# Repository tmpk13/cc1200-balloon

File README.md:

# cc1200-balloon

High altitude balloon payload: a CC1200 434 MHz telemetry downlink, an
AT6558R GNSS receiver and an air quality sensor stack, hosted by a Seeed
Wio-E5 module on a four-layer 50 x 30 mm KiCad board. The board is routed
but not cleared for fabrication: read the verdict table in `BOARD_REVIEW.md`
before ordering. The hand-edited `.kicad_sch` files are the source of truth;
`build.sh` and `sheets/*.json` still describe the 2026-09-06 design, so do
not run `build.sh`: it would overwrite all four sheets with it.

- `mise run erc`: full-hierarchy ERC into `build/erc.rpt`
- `mise run drc`: DRC with zones refilled in memory and schematic parity, into `build/drc.rpt`
- `mise run fields-check`: report the part fields `mise run fields` would change
- `mise run fields`: write `Datasheet`, `MPN` and `Manufacturer` from `tools/parts.json` into the sheets and the board
- `mise run bom`: regenerate `digikey_bom.csv`, `BOM.md` and `bom.json` from the schematic
- `mise run power`: battery budget for the as-built, LDO and switched-domain power options
- `mise run test`: tests for the power budget and the label localizer

`mise tasks` lists the rest. Components: ARCHITECTURE.md. Open items: TODO.md.

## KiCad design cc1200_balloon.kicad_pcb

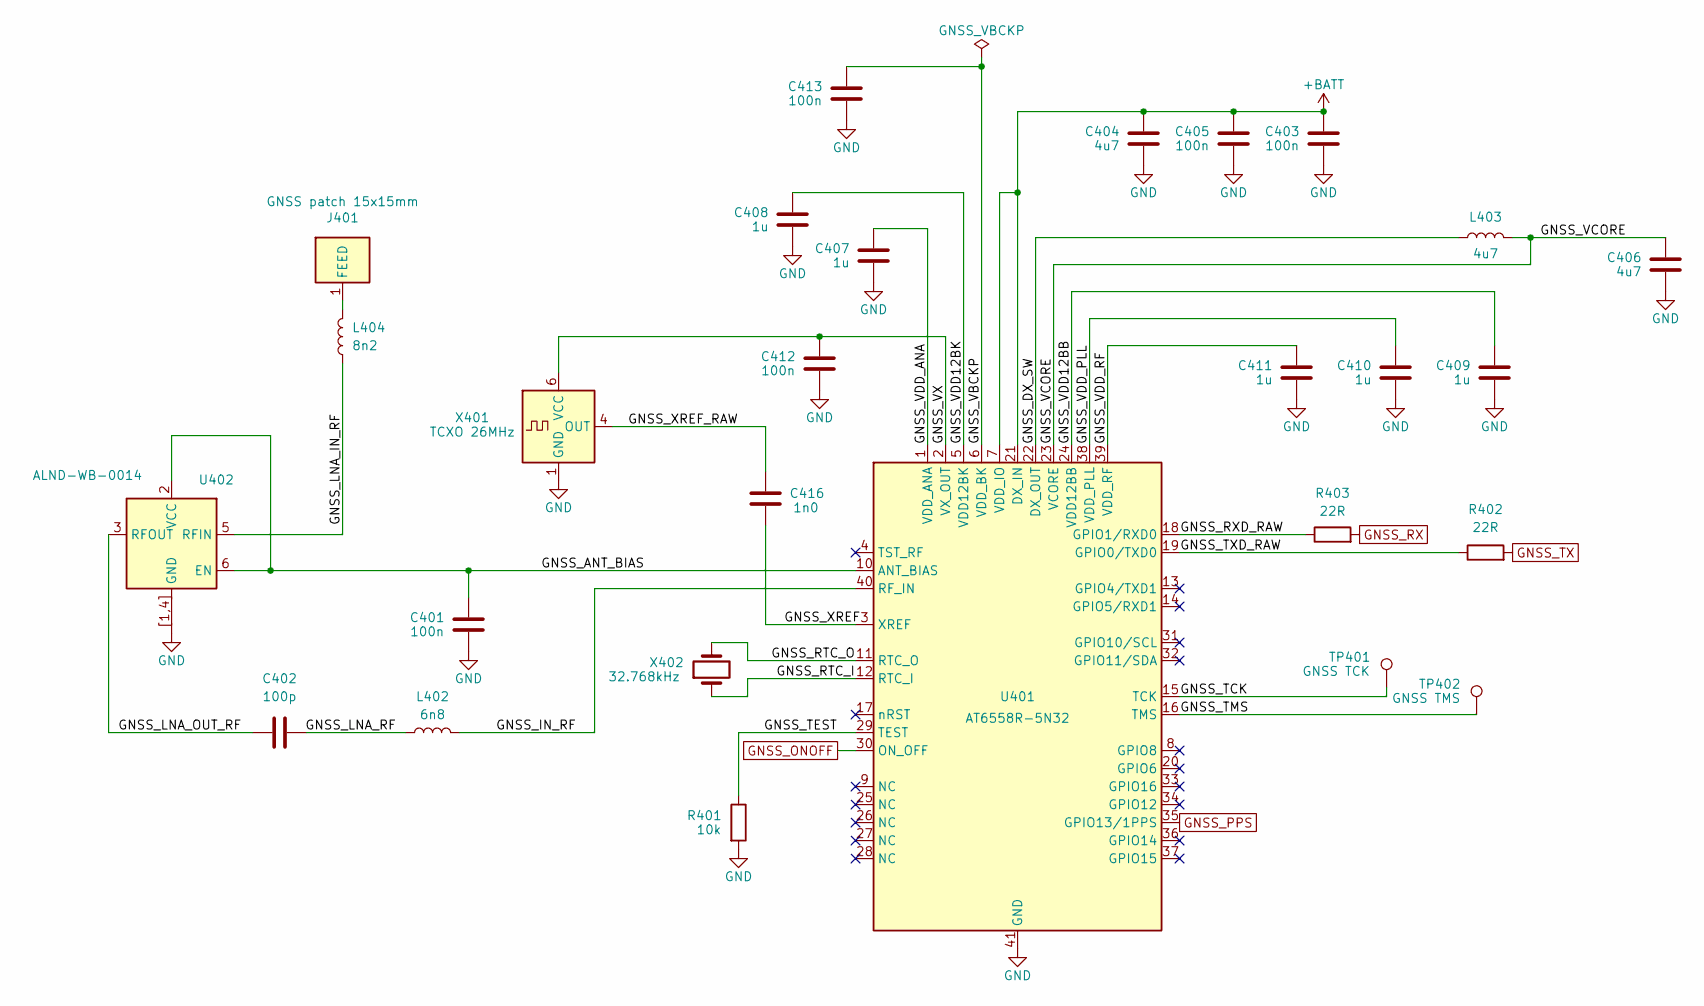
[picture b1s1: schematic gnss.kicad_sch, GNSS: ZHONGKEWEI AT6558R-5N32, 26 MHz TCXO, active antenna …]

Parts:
C401, C403, C405, C412, C413: 100n; C_0402_1005Metric; MPN CL05B104KO5NNNC
C402: 100p; C_0402_1005Metric; MPN GRM1555C1H101JA01D
C404, C406: 4u7; C_0603_1608Metric; MPN LMK107BJ475KAHT
C407, C408, C409, C410, C411: 1u; C_0402_1005Metric; MPN LMK105BJ105KVHF
C416: 1n0; C_0402_1005Metric; MPN CL05C102JB5NNNC
J401: GNSS patch 15x15mm; Patch_AC33154-1T_15x15mm; MPN AC33154-1T
L402: 6n8; L_0402_1005Metric; MPN LQW15AN6N8H00D
L403: 4u7; L_0603_1608Metric; MPN LQM18PN4R7MFRL
L404: 8n2; L_0402_1005Metric; MPN LQW15AN8N2H00D
R401: 10k; R_0402_1005Metric; MPN RC0402FR-0710KL
R402, R403: 22R; R_0402_1005Metric; MPN RC0402FR-0722RL
TP401: GNSS TCK; TestPoint_Pad_1.0x1.0mm
TP402: GNSS TMS; TestPoint_Pad_1.0x1.0mm
U401: AT6558R-5N32; AT6558R_QFN-40-1EP_5x5mm_P0.4mm_EP3.4x3.4mm; MPN AT6558R-5N32
U402: ALND-WB-0014; Abracon_DFN-6_1.1x0.7mm; MPN ALND-WB-0014-T
X401: TCXO 26MHz; Oscillator_SMD_Kyocera_2520-6Pin_2.5x2.0mm; MPN NSC5351B-26M
X402: 32.768kHz; Crystal_SMD_3215-2Pin_3.2x1.5mm; MPN FC3215AN 32.768K-90NN60KC5

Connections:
+BATT: C403.1, C404.1, C405.1, U401.7 (VDD_IO), U401.21 (DX_IN); also elsewhere on the board
/GNSS/GNSS_ANT_BIAS: C401.1, U401.10 (ANT_BIAS), U402.2 (VCC), U402.6 (EN)
/GNSS/GNSS_DX_SW: L403.1, U401.22 (DX_OUT)
/GNSS/GNSS_IN_RF: L402.2, U401.40 (RF_IN)
/GNSS/GNSS_LNA_IN_RF: L404.1, U402.5 (RFIN)
/GNSS/GNSS_LNA_OUT_RF: C402.1, U402.3 (RFOUT)
/GNSS/GNSS_LNA_RF: C402.2, L402.1
/GNSS/GNSS_RTC_I: U401.12 (RTC_I), X402.1
/GNSS/GNSS_RTC_O: U401.11 (RTC_O), X402.2
/GNSS/GNSS_RXD_RAW: R403.1, U401.18 (GPIO1/RXD0)
/GNSS/GNSS_TCK: TP401.1 (1_1), U401.15 (TCK)
/GNSS/GNSS_TEST: R401.1, U401.29 (TEST)
/GNSS/GNSS_TMS: TP402.1 (1_1), U401.16 (TMS)
/GNSS/GNSS_TXD_RAW: R402.1, U401.19 (GPIO0/TXD0)
/GNSS/GNSS_VBCKP: C413.1, U401.6 (VDD_BK)
/GNSS/GNSS_VCORE: C406.1, L403.2, U401.23 (VCORE)
/GNSS/GNSS_VDD12BB: C409.1, U401.24 (VDD12BB)
/GNSS/GNSS_VDD12BK: C408.1, U401.5 (VDD12BK)
/GNSS/GNSS_VDD_ANA: C407.1, U401.1 (VDD_ANA)
/GNSS/GNSS_VDD_PLL: C410.1, U401.38 (VDD_PLL)
/GNSS/GNSS_VDD_RF: C411.1, U401.39 (VDD_RF)
/GNSS/GNSS_VX: C412.1, U401.2 (VX_OUT), X401.6 (VCC)
/GNSS/GNSS_XREF: C416.2, U401.3 (XREF)
/GNSS/GNSS_XREF_RAW: C416.1, X401.4 (OUT)
GND: C401.2, C403.2, C404.2, C405.2, C406.2, C407.2, C408.2, C409.2, C410.2, C411.2, C412.2, C413.2, R401.2, U401.41 (GND), U402.1 (GND), U402.4 (GND), U402.[1,4] (GND), X401.1 (GND), X401.3 (GND); also elsewhere on the board
GNSS_ONOFF: U401.30 (ON_OFF); also elsewhere on the board
GNSS_PPS: U401.35 (GPIO13/1PPS); also elsewhere on the board
GNSS_RX: R403.2; also elsewhere on the board
GNSS_TX: R402.2; also elsewhere on the board
unnamed: J401.1 (FEED_1), L404.2

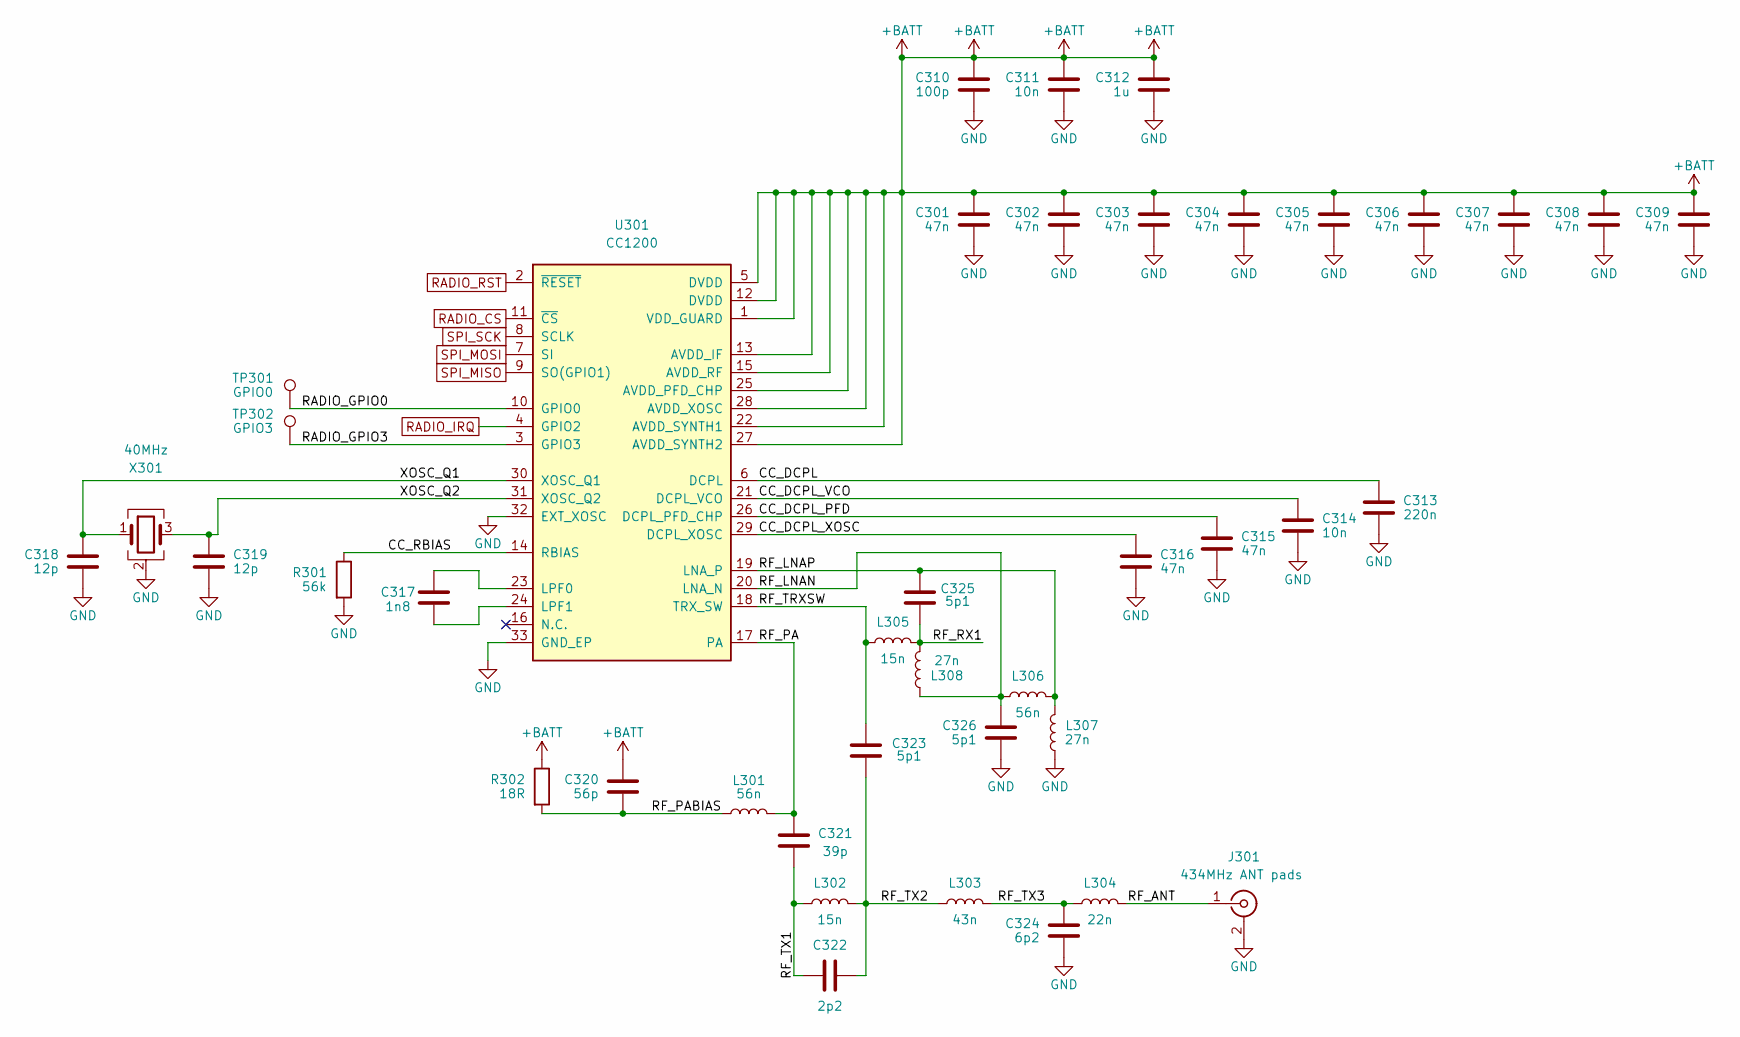
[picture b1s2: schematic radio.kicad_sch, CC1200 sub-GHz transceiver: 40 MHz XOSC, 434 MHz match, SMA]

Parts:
C301, C302, C303, C304, C305, C306, C307, C308, C309, C315, C316: 47n; C_0402_1005Metric; MPN GRM155R71H473KE14D
C310: 100p; C_0402_1005Metric; MPN GRM1555C1H101JA01D
C311, C314: 10n; C_0402_1005Metric; MPN GRM155R71H103KA88D
C312: 1u; C_0402_1005Metric; MPN LMK105BJ105KVHF
C313: 220n; C_0402_1005Metric; MPN CL05A224KA5NNNC
C317: 1n8; C_0402_1005Metric; MPN GRM1555C1H182JA01D
C318, C319: 12p; C_0402_1005Metric; MPN CL05C120JB5NNNC
C320: 56p; C_0402_1005Metric; MPN GRM1555C1H560JA01D
C321: 39p; C_0402_1005Metric; MPN CC0402JRNPO9BN390
C322: 2p2; C_0402_1005Metric; MPN GRM1555C1H2R2BA01D
C323, C325, C326: 5p1; C_0402_1005Metric; MPN GJM1555C1H5R1CB01D
C324: 6p2; C_0402_1005Metric; MPN GJM1555C1H6R2BB01D
J301: 434MHz ANT pads; SMA_Samtec_SMA-J-P-H-ST-EM1_EdgeMount; MPN SMA-J-P-H-ST-EM1
L301, L306: 56n; L_0402_1005Metric; MPN LQW15AN56NH00D
L302, L305: 15n; L_0402_1005Metric; MPN LQW15AN15NJ00D
L303: 43n; L_0402_1005Metric; MPN LQW15AN43NG00D
L304: 22n; L_0402_1005Metric; MPN LQW15AN22NG00D
L307, L308: 27n; L_0402_1005Metric; MPN LQW15AN27NG00D
R301: 56k; R_0402_1005Metric; MPN RC0402FR-0756KL
R302: 18R; R_0402_1005Metric; MPN RC0402FR-0718RL
TP301: GPIO0; TestPoint_Pad_1.0x1.0mm
TP302: GPIO3; TestPoint_Pad_1.0x1.0mm
U301: CC1200; Texas_RHB0032E_VQFN-32-1EP_5x5mm_P0.5mm_EP3.45x3.45mm; MPN CC1200RHBR
X301: 40MHz; Crystal_SMD_3225-4Pin_3.2x2.5mm; MPN CX3225SB40000D0FPLCC

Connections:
+BATT: C301.1, C302.1, C303.1, C304.1, C305.1, C306.1, C307.1, C308.1, C309.1, C310.1, C311.1, C312.1, C320.1, R302.1, U301.1 (VDD_GUARD), U301.5 (DVDD), U301.12 (DVDD), U301.13 (AVDD_IF), U301.15 (AVDD_RF), U301.22 (AVDD_SYNTH1), U301.25 (AVDD_PFD_CHP), U301.27 (AVDD_SYNTH2), U301.28 (AVDD_XOSC); also elsewhere on the board
/CC1200 Radio/CC_DCPL: C313.1, U301.6 (DCPL)
/CC1200 Radio/CC_DCPL_PFD: C315.1, U301.26 (DCPL_PFD_CHP)
/CC1200 Radio/CC_DCPL_VCO: C314.1, U301.21 (DCPL_VCO)
/CC1200 Radio/CC_DCPL_XOSC: C316.1, U301.29 (DCPL_XOSC)
/CC1200 Radio/CC_RBIAS: R301.1, U301.14 (RBIAS)
/CC1200 Radio/RADIO_GPIO0: TP301.1 (1_1), U301.10 (GPIO0)
/CC1200 Radio/RADIO_GPIO3: TP302.1 (1_1), U301.3 (GPIO3)
/CC1200 Radio/RF_ANT: J301.1 (In), L304.2
/CC1200 Radio/RF_LNAN: C326.1, L306.2, L308.1, U301.20 (LNA_N)
/CC1200 Radio/RF_LNAP: C325.2, L306.1, L307.1, U301.19 (LNA_P)
/CC1200 Radio/RF_PA: C321.2, L301.2, U301.17 (PA)
/CC1200 Radio/RF_PABIAS: C320.2, L301.1, R302.2
/CC1200 Radio/RF_RX1: C325.1, L305.2, L308.2
/CC1200 Radio/RF_TRXSW: C323.2, L305.1, U301.18 (TRX_SW)
/CC1200 Radio/RF_TX1: C321.1, C322.1, L302.1
/CC1200 Radio/RF_TX2: C322.2, C323.1, L302.2, L303.1
/CC1200 Radio/RF_TX3: C324.2, L303.2, L304.1
/CC1200 Radio/XOSC_Q1: C318.1, U301.30 (XOSC_Q1), X301.1
/CC1200 Radio/XOSC_Q2: C319.1, U301.31 (XOSC_Q2), X301.3
GND: C301.2, C302.2, C303.2, C304.2, C305.2, C306.2, C307.2, C308.2, C309.2, C310.2, C311.2, C312.2, C313.2, C314.2, C315.2, C316.2, C318.2, C319.2, C324.1, C326.2, J301.2 (Ext), L307.2, R301.2, U301.32 (EXT_XOSC), U301.33 (GND_EP), X301.2 (G), X301.4 (G); also elsewhere on the board
unnamed: C317.2, U301.23 (LPF0)
unnamed: C317.1, U301.24 (LPF1)
RADIO_CS: U301.11 (~CS); also elsewhere on the board
RADIO_IRQ: U301.4 (GPIO2); also elsewhere on the board
RADIO_RST: U301.2 (~RESET); also elsewhere on the board
SPI_MISO: U301.9 (SO(GPIO1)); also elsewhere on the board
SPI_MOSI: U301.7 (SI); also elsewhere on the board
SPI_SCK: U301.8 (SCLK); also elsewhere on the board

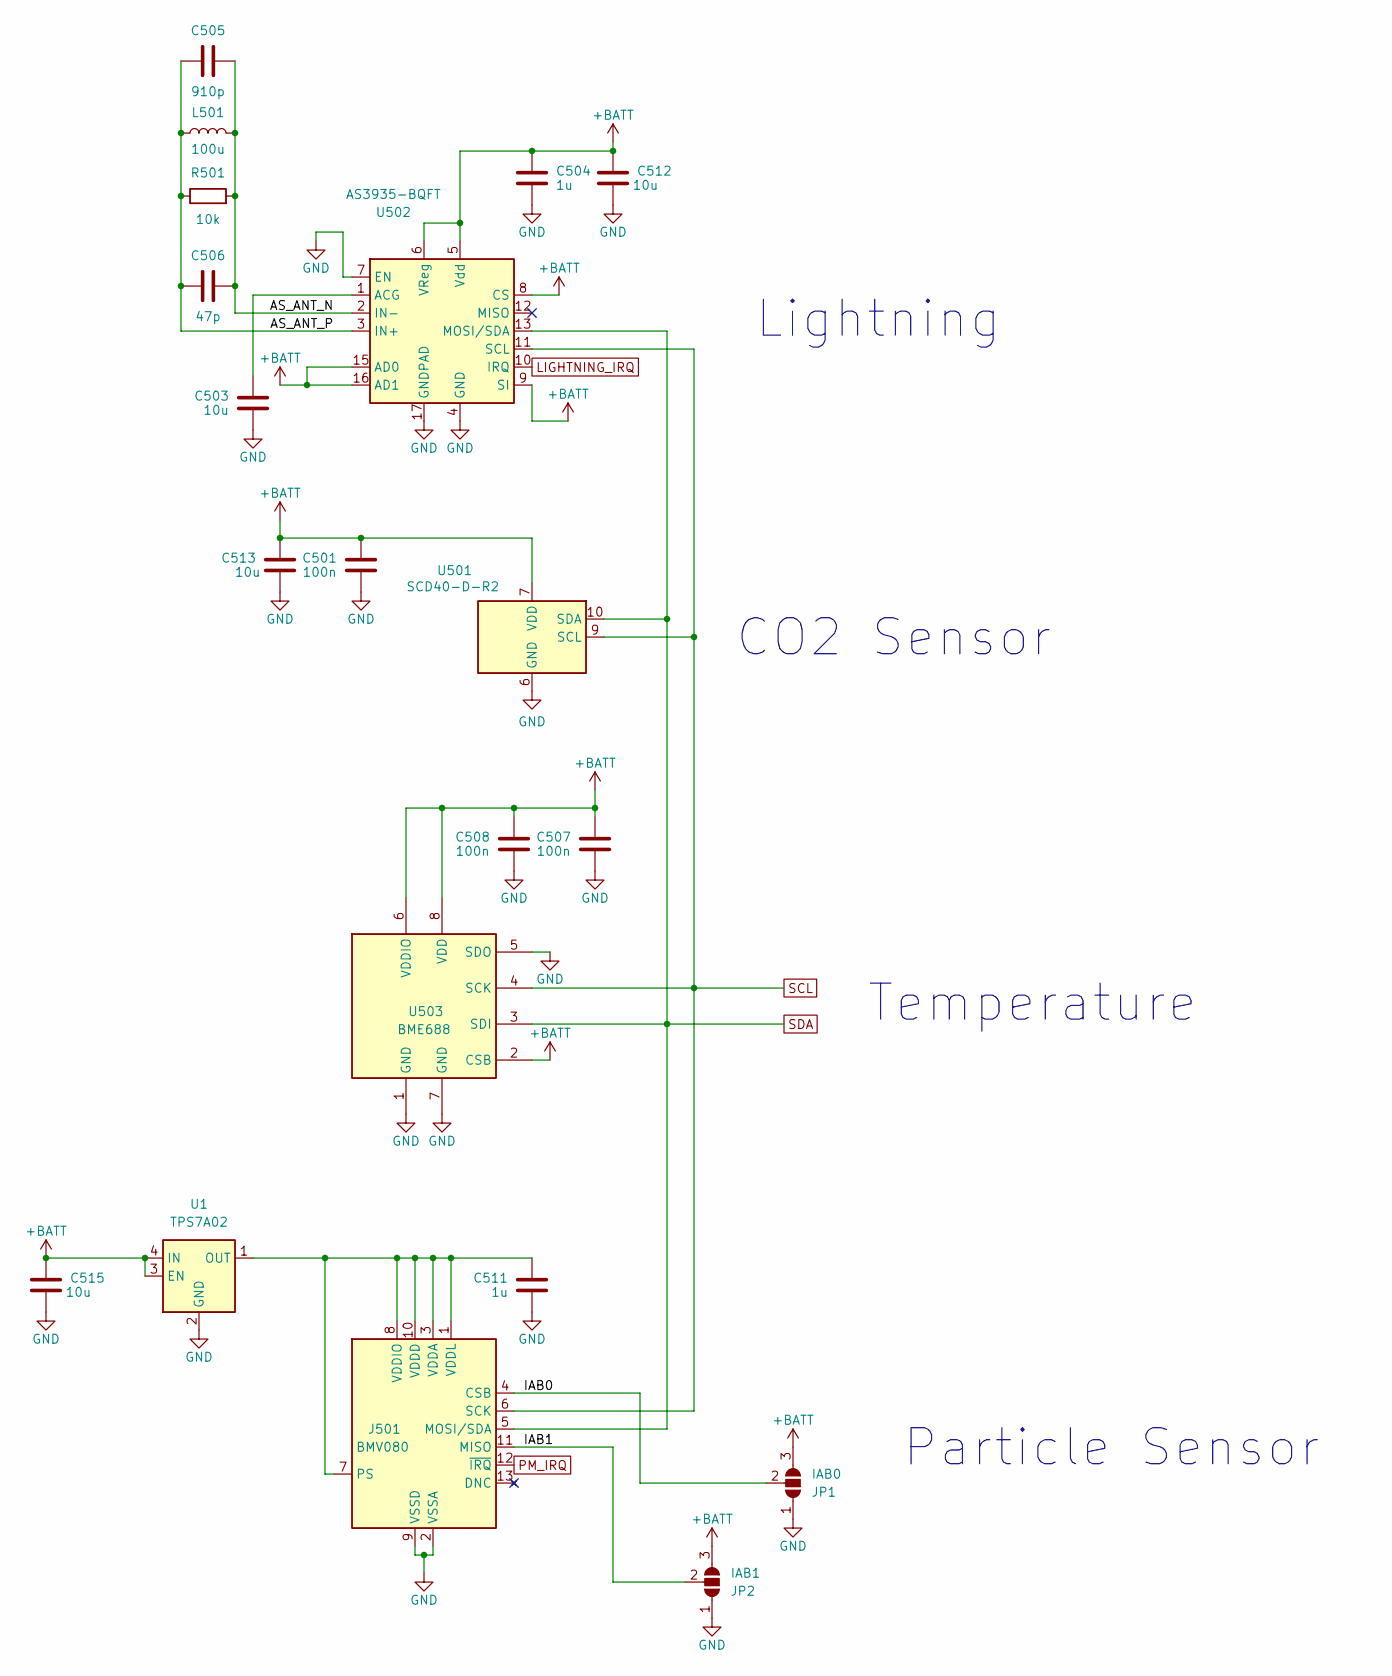
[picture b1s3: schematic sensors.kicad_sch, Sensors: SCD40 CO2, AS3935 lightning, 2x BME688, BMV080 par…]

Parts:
C501, C507, C508: 100n; C_0402_1005Metric; MPN CL05B104KO5NNNC
C503: 10u; C_0603_1608Metric; MPN GRM188R60J106KE47D
C504, C511: 1u; C_0402_1005Metric; MPN LMK105BJ105KVHF
C505: 910p; C_0402_1005Metric; MPN GCM1555C1H911FA16J
C506: 47p; C_0402_1005Metric; MPN CC0402JRNPO9BN470
C512, C513, C515: 10u; C_0402_1005Metric; MPN GRM155R60J106ME15J
J501: BMV080; Kyocera_046844713002846_FPC-13_P0.30mm; MPN 046844713002846+
JP1: IAB0; Jumper_3_0402
JP2: IAB1; Jumper_3_0402
L501: 100u; L_Axial_D2.8mm_L7.2mm_P10.16mm_Horizontal; MPN 78F101J-RC
R501: 10k; R_0402_1005Metric; MPN RC0402FR-0710KL
U1: TPS7A02; Texas_X2SON-4_1x1mm_P0.65mm
U501: SCD40-D-R2; Sensirion_SCD4x-1EP_10.1x10.1mm_P1.25mm_EP4.8x4.8mm; MPN SCD40-D-R2
U502: AS3935-BQFT; QFN-16-1EP_4x4mm_P0.65mm_EP2.7x2.7mm; MPN AS3935-BQFT
U503: BME688; Bosch_LGA-8_3x3mm_P0.8mm_ClockwisePinNumbering; MPN BME688

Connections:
+BATT: C501.1, C504.1, C507.1, C508.1, C512.1, C513.1, C515.1, JP1.3 (B), JP2.3 (B), U1.3 (EN), U1.4 (IN), U501.7 (VDD), U501.19 (VDD), U502.5 (Vdd), U502.6 (VReg), U502.8 (CS), U502.9 (SI), U502.15 (AD0), U502.16 (AD1), U503.2 (CSB), U503.6 (VDDIO), U503.8 (VDD); also elsewhere on the board
/Sensors/AS_ANT_N: C505.2, C506.2, L501.2, R501.2, U502.2 (IN-)
/Sensors/AS_ANT_P: C505.1, C506.1, L501.1, R501.1, U502.3 (IN+)
/Sensors/IAB0: J501.4 (CSB), JP1.2 (C)
/Sensors/IAB1: J501.11 (MISO), JP2.2 (C)
GND: C501.2, C503.2, C504.2, C507.2, C508.2, C511.2, C512.2, C513.2, C515.2, J501.2 (VSSA), J501.9 (VSSD), JP1.1 (A), JP2.1 (A), U1.2 (GND), U501.6 (GND), U501.20 (GND), U501.21 (GND), U502.4 (GND), U502.7 (EN), U502.17 (GNDPAD), U503.1 (GND), U503.5 (SDO), U503.7 (GND); also elsewhere on the board
LIGHTNING_IRQ: U502.10 (IRQ); also elsewhere on the board
unnamed: C511.1, J501.1 (VDDL), J501.3 (VDDA), J501.7 (PS), J501.8 (VDDIO), J501.10 (VDDD), U1.1 (OUT)
unnamed: C503.1, U502.1 (ACG)
PM_IRQ: J501.12 (~IRQ); also elsewhere on the board
SCL: J501.6 (SCK), U501.9 (SCL), U502.11 (SCL), U503.4 (SCK); also elsewhere on the board
SDA: J501.5 (MOSI/SDA), U501.10 (SDA), U502.13 (MOSI/SDA), U503.3 (SDI); also elsewhere on the board

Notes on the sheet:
Temperature
CO2 Sensor
Lightning
Particle Sensor

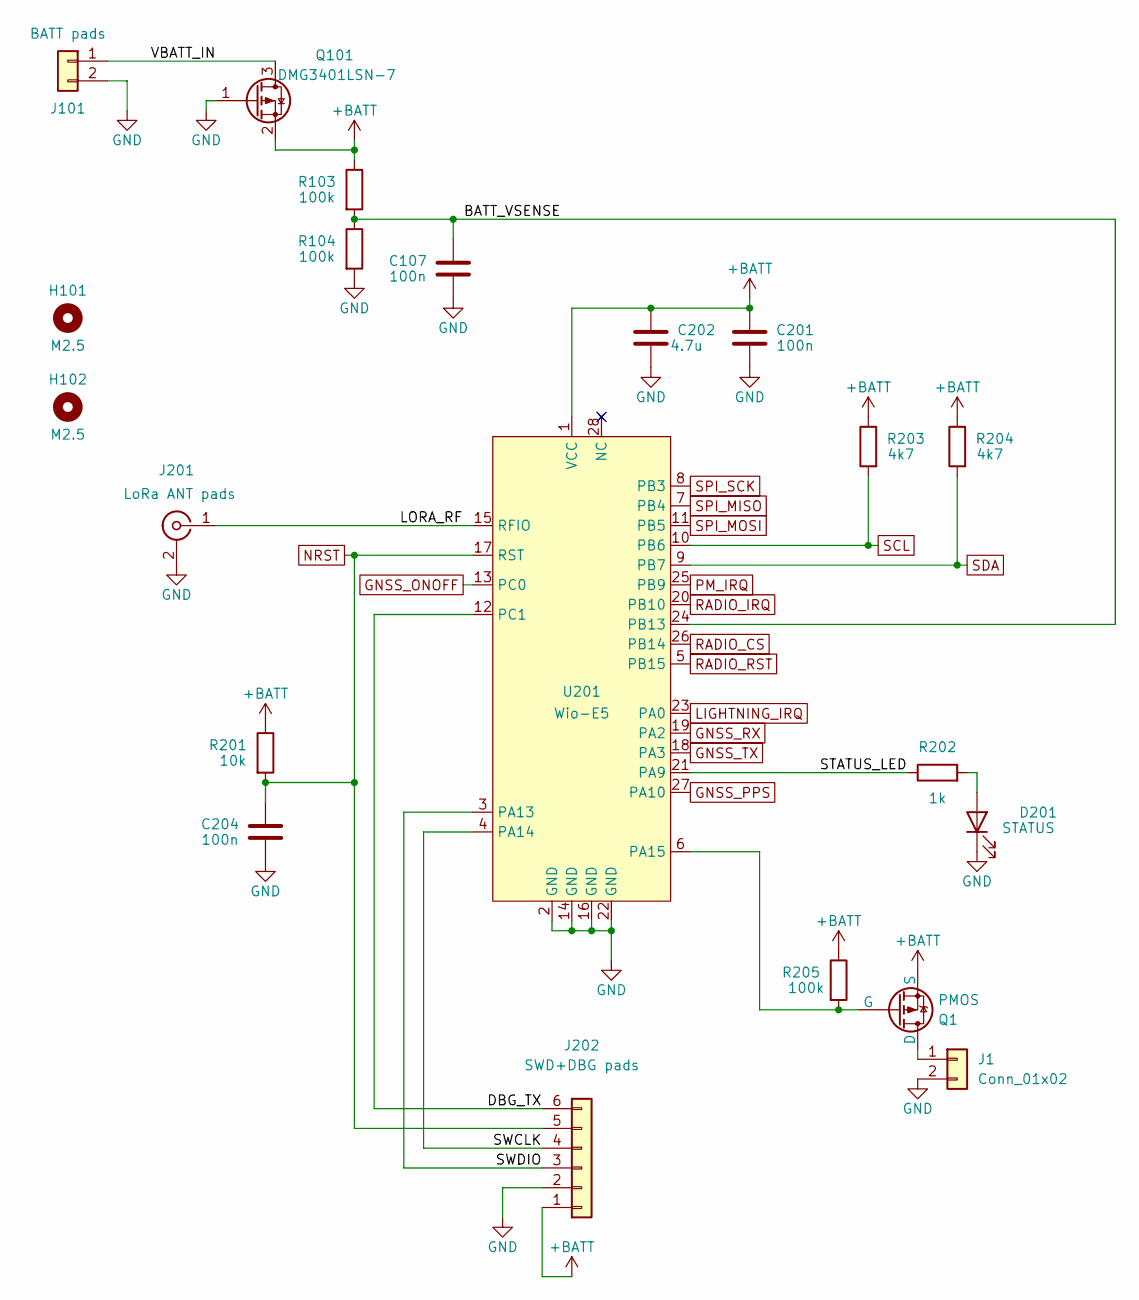
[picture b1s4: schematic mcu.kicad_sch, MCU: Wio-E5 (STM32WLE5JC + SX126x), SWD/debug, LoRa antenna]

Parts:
C107, C201, C204: 100n; C_0402_1005Metric; MPN CL05B104KO5NNNC
C202: 4.7u; C_0402_1005Metric; MPN GRM153R60J475ME15D
D201: STATUS; LED_0402_1005Metric; MPN LTST-C281KGKT-5A
H101, H102: M2.5; MountingHole_2mm
J1: Conn_01x02; PinHeader_1x02_P1.00mm_Vertical
J101: BATT pads; SolderPad_Wire_1x02_P3.0mm
J201: LoRa ANT pads; SMA_Samtec_SMA-J-P-H-ST-EM1_EdgeMount; MPN SMA-J-P-H-ST-EM1
J202: SWD+DBG pads; SolderPad_1x06_P1.27mm
Q1: PMOS; SOT-523; MPN SLMT520V2CP
Q101: DMG3401LSN-7; SOT-23; MPN DMG3401LSN-7
R103, R104, R205: 100k; R_0402_1005Metric; MPN RC0402FR-07100KL
R201: 10k; R_0402_1005Metric; MPN RC0402FR-0710KL
R202: 1k; R_0402_1005Metric; MPN RC0402FR-071KL
R203, R204: 4k7; R_0402_1005Metric; MPN RC0402FR-074K7L
U201: Wio-E5; WIO-E5; MPN 114993120

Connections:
+BATT: C201.1, C202.1, J202.1, Q1.2 (S), Q101.2 (S), R103.1, R201.1, R203.1, R204.1, R205.1, U201.1 (VCC); also elsewhere on the board
/MCU/BATT_VSENSE: C107.1, R103.2, R104.1, U201.24 (PB13)
/MCU/DBG_TX: J202.6, U201.12 (PC1)
/MCU/LORA_RF: J201.1 (In), U201.15 (RFIO)
/MCU/STATUS_LED: R202.1, U201.21 (PA9)
/MCU/SWCLK: J202.4, U201.4 (PA14)
/MCU/SWDIO: J202.3, U201.3 (PA13)
/MCU/VBATT_IN: J101.1, Q101.3 (D)
GND: C107.2, C201.2, C202.2, C204.2, D201.1 (K), J1.2, J101.2, J201.2 (Ext), J202.2, Q101.1 (G), R104.2, U201.2 (GND), U201.14 (GND), U201.16 (GND), U201.22 (GND); also elsewhere on the board
GNSS_ONOFF: U201.13 (PC0); also elsewhere on the board
GNSS_PPS: U201.27 (PA10); also elsewhere on the board
GNSS_RX: U201.19 (PA2); also elsewhere on the board
GNSS_TX: U201.18 (PA3); also elsewhere on the board
LIGHTNING_IRQ: U201.23 (PA0); also elsewhere on the board
NRST: C204.1, J202.5, R201.2, U201.17 (RST)
unnamed: D201.2 (A), R202.2
unnamed: J1.1, Q1.3 (D)
unnamed: Q1.1 (G), R205.2, U201.6 (PA15)
PM_IRQ: U201.25 (PB9); also elsewhere on the board
RADIO_CS: U201.26 (PB14); also elsewhere on the board
RADIO_IRQ: U201.20 (PB10); also elsewhere on the board
RADIO_RST: U201.5 (PB15); also elsewhere on the board
SCL: R203.2, U201.10 (PB6); also elsewhere on the board
SDA: R204.2, U201.9 (PB7); also elsewhere on the board
SPI_MISO: U201.7 (PB4); also elsewhere on the board
SPI_MOSI: U201.11 (PB5); also elsewhere on the board
SPI_SCK: U201.8 (PB3); also elsewhere on the board

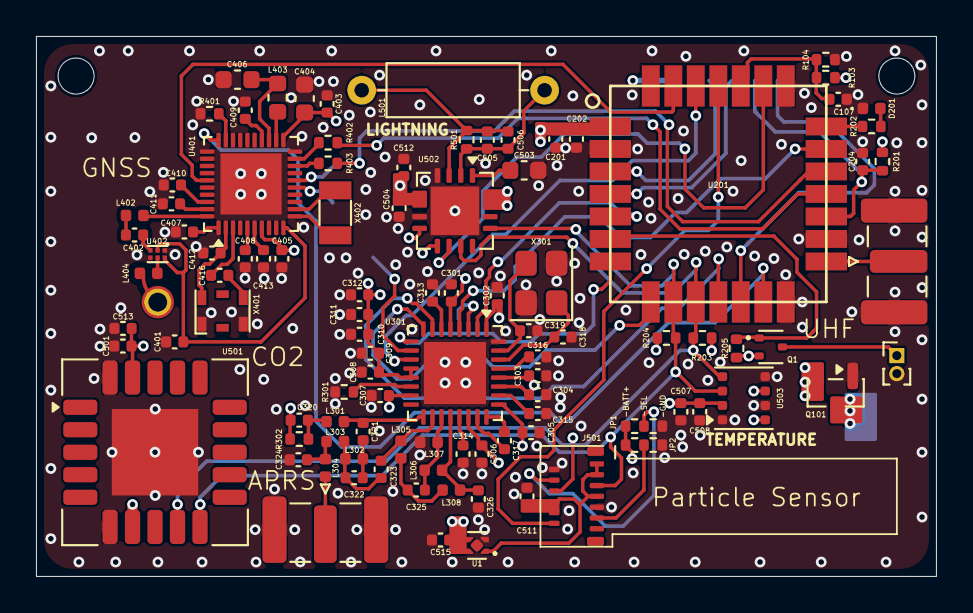
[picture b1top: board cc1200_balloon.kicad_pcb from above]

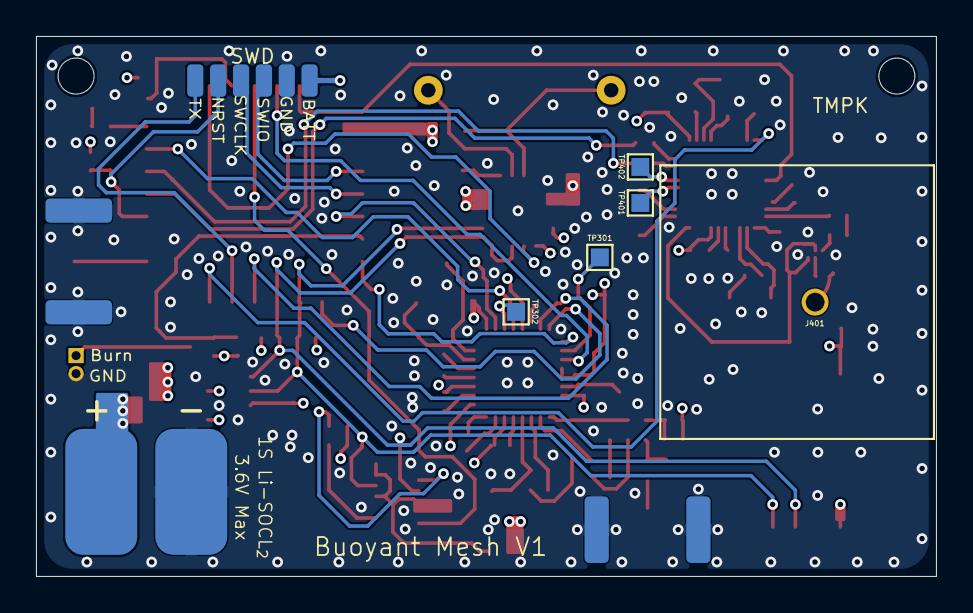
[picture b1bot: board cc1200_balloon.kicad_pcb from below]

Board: 4 copper layers, 50.0 x 30.0 mm, 109 parts (7 on the bottom side), 78 nets.

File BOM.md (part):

# cc1200-balloon bill of materials

Generated 2026-09-22 from the schematic by `tools/gen_digikey_bom.py`. 53 lines, 98 placements, 52 lines in `digikey_bom.csv`.

**Quantities are for 1 board. Set the multiplier in DigiKey's BOM Manager rather than scaling the file.** Nothing is rounded up to a pack or a reel.

Unit prices are DigiKey cut-tape prices at quantity 1 on the date shown in the last column; stock is what DigiKey listed that day. Where DigiKey only exposed the reel listing, the cut-tape number is derived (`-1-ND` / `CT-ND`) and the stock figure is the reel's. Indicative, not a quote.

**Board total (excluding DNP): $107.21** - lines without a price: GRM1555C1H2R2BA01D, AT6558R-5N32

| Refs | Value | MPN | Manufacturer | Package | Qty | DigiKey | Packaging | Stock | Unit | Read |
| --- | --- | --- | --- | --- | --- | --- | --- | --- | --- | --- |
| C107 C201 C204 C401 C403 C405 C412 C413 C501 C507 C508 | 100n | CL05B104KO5NNNC | Samsung Electro-Mechanics | C_0402_1005Metric | 11 | 1276-1001-1-ND | Cut Tape | 1691012 | $0.0170 | 2026-08-25 |
| C202 | 4.7u | GRM153R60J475ME15D | Murata Electronics | C_0402_1005Metric | 1 | 490-13232-1-ND | Cut Tape | 5661 | $0.1400 | 2026-09-15 |
| C301 C302 C303 C304 C305 C306 C307 C308 C309 C315 C316 | 47n | GRM155R71H473KE14D | Murata Electronics | C_0402_1005Metric | 11 | 490-10702-1-ND | Cut Tape | 879037 | $0.0230 | 2026-08-25 |
| C310 C402 | 100p | GRM1555C1H101JA01D | Murata Electronics | C_0402_1005Metric | 2 | 490-5922-1-ND | Cut Tape | 127396 | $0.1100 | 2026-08-25 |
| C311 C314 | 10n | GRM155R71H103KA88D | Murata Electronics | C_0402_1005Metric | 2 | 490-4516-1-ND | Cut Tape | 2804857 | $0.1000 | 2026-08-25 |
| C312 C407 C408 C409 C410 C411 C504 C511 | 1u | LMK105BJ105KVHF | Taiyo Yuden | C_0402_1005Metric | 8 | 587-3712-1-ND | Cut Tape | 726374 | $0.0560 | 2026-08-25 |
| C313 | 220n | CL05A224KA5NNNC | Samsung Electro-Mechanics | C_0402_1005Metric | 1 | 1276-1455-1-ND | Cut Tape | 1498 | $0.1700 | 2026-09-15 |
| C317 | 1n8 | GRM1555C1H182JA01D | Murata Electronics | C_0402_1005Metric | 1 | 490-GRM1555C1H182JA01DCT-ND | Cut Tape | 149784 | $0.1000 | 2026-08-25 |
| C318 C319 | 12p | CL05C120JB5NNNC | Samsung Electro-Mechanics | C_0402_1005Metric | 2 | 1276-1178-1-ND | Cut Tape | 95232 | $0.1000 | 2026-08-25 |
| C320 | 56p | GRM1555C1H560JA01D | Murata Electronics | C_0402_1005Metric | 1 | 490-1288-1-ND | Cut Tape | 980312 | $0.1000 | 2026-08-25 |
| C321 | 39p | CC0402JRNPO9BN390 | YAGEO | C_0402_1005Metric | 1 | 311-1009-1-ND | Cut Tape | 226457 | $0.1000 | 2026-08-25 |
| C322 | 2p2 | GRM1555C1H2R2BA01D | Murata Electronics | C_0402_1005Metric | 1 | 490-6227-1-ND | Cut Tape | 411273 | - | 2026-09-15 |
| C323 C325 C326 | 5p1 | GJM1555C1H5R1CB01D | Murata Electronics | C_0402_1005Metric | 3 | 490-3102-1-ND | Cut Tape | 166550 | $0.1000 | 2026-08-25 |
| C324 | 6p2 | GJM1555C1H6R2BB01D | Murata Electronics | C_0402_1005Metric | 1 | 490-11231-1-ND | Cut Tape | 436522 | $0.1000 | 2026-08-25 |
| C404 C406 | 4u7 | LMK107BJ475KAHT | Taiyo Yuden | C_0603_1608Metric | 2 | 587-3416-1-ND | Cut Tape | 1292 | $0.1700 | 2026-09-15 |
| C416 | 1n0 | CL05C102JB5NNNC | Samsung Electro-Mechanics | C_0402_1005Metric | 1 | 1276-1635-1-ND | Cut Tape | 22 | $0.1200 | 2026-09-22 |
| C503 | 10u | GRM188R60J106KE47D | Murata Electronics | C_0603_1608Metric | 1 | 490-12538-1-ND | Cut Tape | 49549 | $0.1200 | 2026-08-25 |
| C505 | 910p | GCM1555C1H911FA16J | Murata Electronics | C_0402_1005Metric | 1 | 490-GCM1555C1H911FA16JCT-ND | Cut Tape | 62400 | $0.1000 | 2026-08-25 |
| C506 | 47p | CC0402JRNPO9BN470 | YAGEO | C_0402_1005Metric | 1 | 311-1021-1-ND | Cut Tape | 256016 | $0.1000 | 2026-08-25 |
| C512 C513 C515 | 10u | GRM155R60J106ME15J | Murata Electronics | C_0402_1005Metric | 3 | 490-GRM155R60J106ME15JCT-ND | Cut Tape | 35790 | $0.1700 | 2026-09-22 |
| D201 | STATUS | LTST-C281KGKT-5A | Lite-On Inc. | LED_0402_1005Metric | 1 | 160-LTST-C281KGKT-5ACT-ND | Cut Tape | 523 | $0.3100 | 2026-09-15 |
| J201 J301 | LoRa ANT pads | SMA-J-P-H-ST-EM1 | Samtec Inc. | SMA_Samtec_SMA-J-P-H-ST-EM1_EdgeMount | 2 | SAM8857-ND | Tray | 65112 | $2.6500 | 2026-09-15 |
| J401 | GNSS patch 15x15mm | AC33154-1T | The Antenna Company | Patch_AC33154-1T_15x15mm | 1 | 5350-AC33154-1T-ND | Tray | 998 | $2.4500 | 2026-09-22 |
| J501 | BMV080 | 046844713002846+ | KYOCERA AVX | Kyocera_046844713002846_FPC-13_P0.30mm | 1 | 478-046844713002846+CT-ND | Cut Tape | 27257 | $0.8000 | 2026-08-25 |
| L301 L306 | 56n | LQW15AN56NH00D | Murata Electronics | L_0402_1005Metric | 2 | 490-11765-1-ND | Cut Tape | 4681 | $0.1200 | 2026-09-15 |
| L302 L305 | 15n | LQW15AN15NJ00D | Murata Electronics | L_0402_1005Metric | 2 | 490-1148-1-ND | Cut Tape | 2185 | $0.1100 | 2026-09-15 |
| L303 | 43n | LQW15AN43NG00D | Murata Electronics | L_0402_1005Metric | 1 | 490-6817-1-ND | Cut Tape | 27740 | $0.1200 | 2026-08-25 |
| L304 | 22n | LQW15AN22NG00D | Murata Electronics | L_0402_1005Metric | 1 | 490-6787-1-ND | Cut Tape | 599371 | $0.1200 | 2026-08-25 |
| L307 L308 | 27n | LQW15AN27NG00D | Murata Electronics | L_0402_1005Metric | 2 | 490-6792-1-ND | Cut Tape | 91650 | $0.1200 | 2026-08-25 |
| L402 | 6n8 | LQW15AN6N8H00D | Murata Electronics | L_0402_1005Metric | 1 | 490-6841-1-ND | Cut Tape | 20027 | $0.1100 | 2026-08-25 |
| L403 | 4u7 | LQM18PN4R7MFRL | Murata Electronics | L_0603_1608Metric | 1 | 490-12065-1-ND | Cut Tape | 105827 | $0.1700 | 2026-08-25 |
| L404 | 8n2 | LQW15AN8N2H00D | Murata Electronics | L_0402_1005Metric | 1 | 490-6850-1-ND | Cut Tape | 2864 | $0.1100 | 2026-09-22 |
| L501 | 100u | 78F101J-RC | Bourns Inc. | L_Axial_D2.8mm_L7.2mm_P10.16mm_Horizontal | 1 | M10136-ND | Bulk | 9717 | $0.2200 | 2026-09-15 |
| Q1 | PMOS | SLMT520V2CP | Shenzhen Slkormicro Semicon | SOT-523 | 1 | 5399-SLMT520V2CPCT-ND | Cut Tape | - | $0.1500 | 2026-09-22 |
| Q101 | DMG3401LSN-7 | DMG3401LSN-7 | Diodes Incorporated | SOT-23 | 1 | DMG3401LSN-7DICT-ND | Cut Tape | 150434 | $0.5600 | 2026-08-25 |
| R103 R104 R205 | 100k | RC0402FR-07100KL | YAGEO | R_0402_1005Metric | 3 | 311-100KLRCT-ND | Cut Tape | 7713411 | $0.1000 | 2026-08-25 |
| R201 R401 R501 | 10k | RC0402FR-0710KL | YAGEO | R_0402_1005Metric | 3 | 311-10.0KLRCT-ND | Cut Tape | 11909113 | $0.1000 | 2026-08-25 |
| R202 | 1k | RC0402FR-071KL | YAGEO | R_0402_1005Metric | 1 | 311-1.00KLRCT-ND | Cut Tape | 5662954 | $0.1000 | 2026-08-25 |
| R203 R204 | 4k7 | RC0402FR-074K7L | YAGEO | R_0402_1005Metric | 2 | 311-4.7KLRCT-ND | Cut Tape | 270685 | $0.1000 | 2026-08-25 |
| R301 | 56k | RC0402FR-0756KL | YAGEO | R_0402_1005Metric | 1 | 311-56.0KLRCT-ND | Cut Tape | 663752 | $0.1000 | 2026-08-25 |
| R302 | 18R | RC0402FR-0718RL | YAGEO | R_0402_1005Metric | 1 | YAG3021CT-ND | Cut Tape | 371055 | $0.1000 | 2026-08-25 |
| R402 R403 | 22R | RC0402FR-0722RL | YAGEO | R_0402_1005Metric | 2 | 311-22.0LRCT-ND | Cut Tape | 5263774 | $0.1000 | 2026-08-25 |
| U201 | Wio-E5 | 114993120 | Seeed Technology Co., Ltd | WIO-E5 | 1 | 1597-114993120-ND | Box | 476 | $7.1100 | 2026-09-15 |
| U301 | CC1200 | CC1200RHBR | Texas Instruments | Texas_RHB0032E_VQFN-32-1EP_5x5mm_P0.5mm_EP3.45x3.45mm | 1 | 296-38892-1-ND | Cut Tape | 5448 | $5.4300 | 2026-08-25 |
| U401 | AT6558R-5N32 | AT6558R-5N32 | Hangzhou Zhongkewei (ICOFCHINA) | AT6558R_QFN-40-1EP_5x5mm_P0.4mm_EP3.4x3.4mm | 1 | - | - | - | - | 2026-09-15 |
| U402 | ALND-WB-0014 | ALND-WB-0014-T | Abracon LLC | Abracon_DFN-6_1.1x0.7mm | 1 | 535-ALND-WB-0014-TCT-ND | Cut Tape | 4927 | $0.3800 | 2026-09-22 |
| U501 | SCD40-D-R2 | SCD40-D-R2 | Sensirion AG | Sensirion_SCD4x-1EP_10.1x10.1mm_P1.25mm_EP4.8x4.8mm | 1 | 1649-SCD40-D-R2CT-ND | Cut Tape | 3496 | $18.6600 | 2026-08-25 |
| U502 | AS3935-BQFT | AS3935-BQFT | ScioSense | QFN-16-1EP_4x4mm_P0.65mm_EP2.7x2.7mm | 1 | AS3935-BQFTCT-ND | Cut Tape | 1421 | $9.3500 | 2026-08-25 |
| U503 | BME688 | BME688 | Bosch Sensortec | Bosch_LGA-8_3x3mm_P0.8mm_ClockwisePinNumbering | 1 | 828-BME688CT-ND | Cut Tape | 5128 | $8.9900 | 2026-08-25 |
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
